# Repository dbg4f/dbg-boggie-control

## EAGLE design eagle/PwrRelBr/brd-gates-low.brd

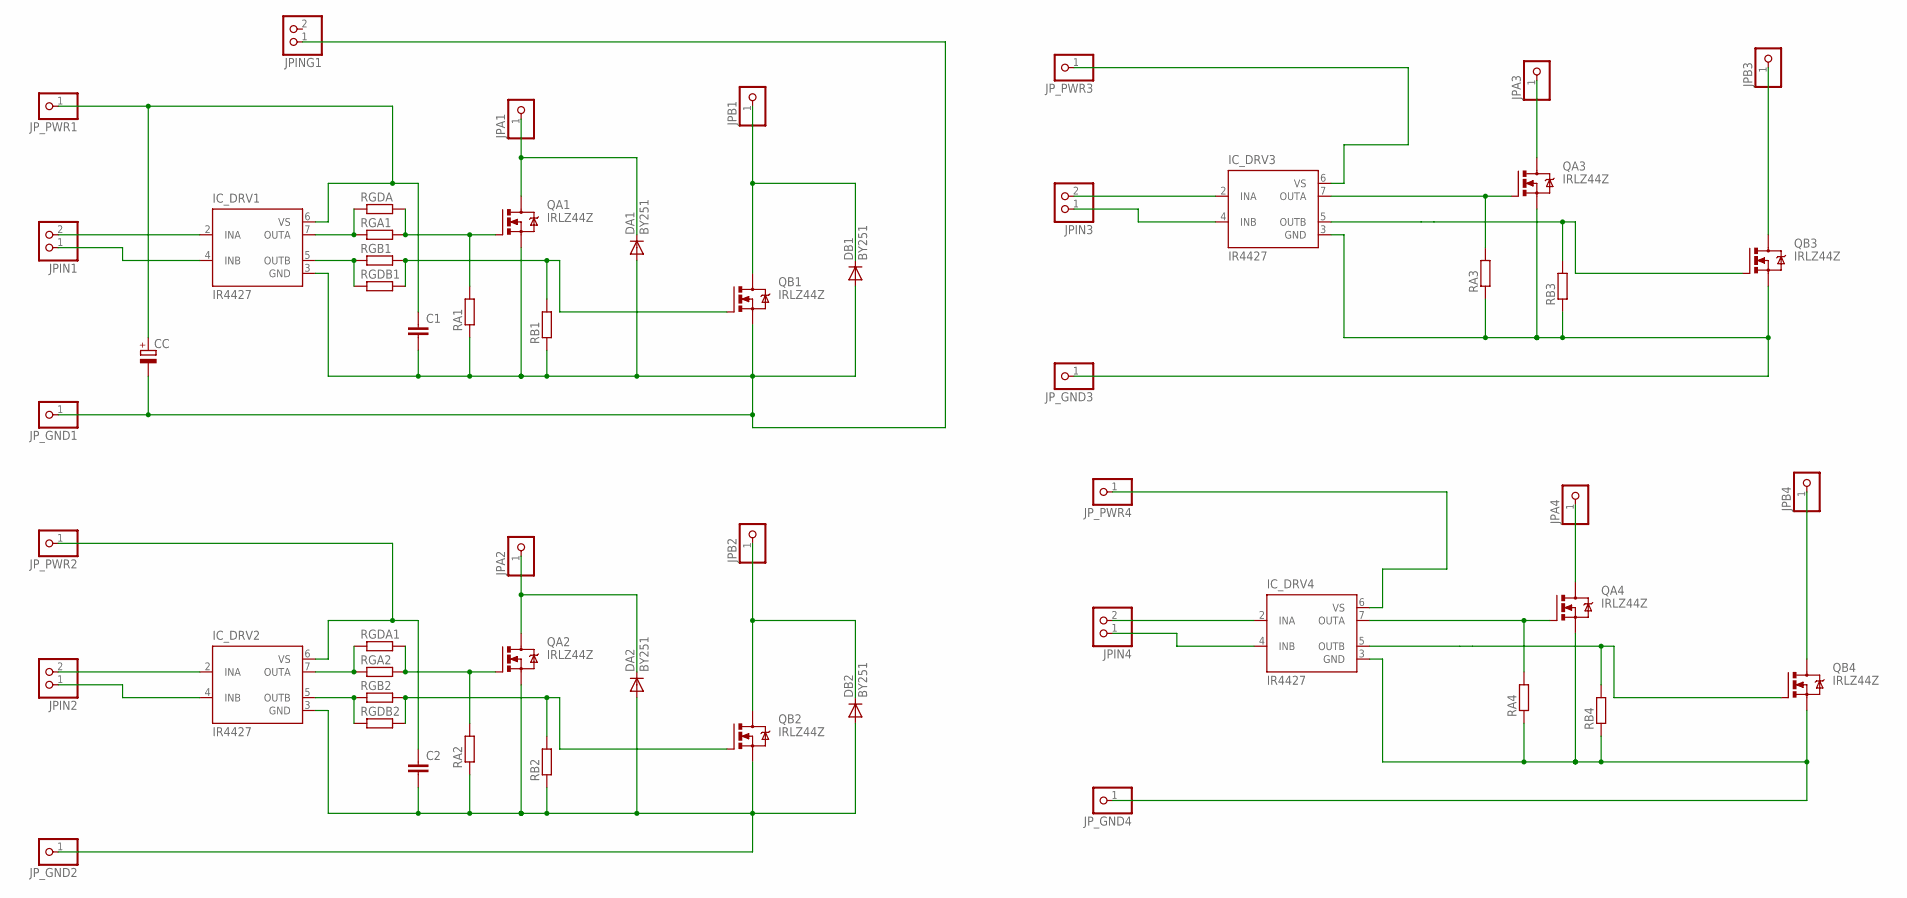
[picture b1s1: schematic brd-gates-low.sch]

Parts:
C1, C2: C-EU050-055X075; C050-055X075
CC: CPOL-EUE5-13; E5-13
DA1, DA2: BY251; DO201-15
DB1, DB2: BY251; DO201-15
IC_DRV1, IC_DRV2, IC_DRV3, IC_DRV4: IR4427; DIL08
JPA1, JPA2, JPA3, JPA4: PINHD-1X1; 1X01
JPB1, JPB2, JPB3, JPB4: PINHD-1X1; 1X01
JPIN1, JPIN2, JPIN3, JPIN4: PINHD-1X2; 1X02
JPING1: PINHD-1X2; 1X02
JP_GND1, JP_GND2, JP_GND3, JP_GND4: PINHD-1X1; 1X01
JP_PWR1, JP_PWR2, JP_PWR3, JP_PWR4: PINHD-1X1; 1X01
QA1, QA2, QA3, QA4: IRLZ44Z; TO220BH
QB1, QB2, QB3, QB4: IRLZ44Z; TO220BH
RA1, RA2, RA3, RA4: R-EU_0207/10; 0207/10
RB1, RB2, RB3, RB4: R-EU_0207/10; 0207/10
RGA1, RGA2: R-EU_0207/10; 0207/10
RGB1, RGB2: R-EU_0207/10; 0207/10
RGDA, RGDA1: R-EU_0207/10; 0207/10
RGDB1, RGDB2: R-EU_0207/10; 0207/10

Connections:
GND: C1.2, CC.-, DA1.A, DB1.A, IC_DRV1.3 (GND), JPING1.1, JP_GND1.1, QA1.S, QB1.S, RA1.1, RB1.1
GND1: C2.2, DA2.A, DB2.A, IC_DRV2.3 (GND), JP_GND2.1, QA2.S, QB2.S, RA2.1, RB2.1
GND2: IC_DRV3.3 (GND), JP_GND3.1, QA3.S, QB3.S, RA3.1, RB3.1
GND3: IC_DRV4.3 (GND), JP_GND4.1, QA4.S, QB4.S, RA4.1, RB4.1
unnamed: IC_DRV1.2 (INA), JPIN1.2
unnamed: IC_DRV1.4 (INB), JPIN1.1
unnamed: IC_DRV1.7 (OUTA), RGA1.1, RGDA.1
unnamed: IC_DRV1.5 (OUTB), RGB1.1, RGDB1.1
unnamed: QA1.G, RA1.2, RGA1.2, RGDA.2
unnamed: QB1.G, RB1.2, RGB1.2, RGDB1.2
unnamed: IC_DRV2.7 (OUTA), RGA2.1, RGDA1.1
unnamed: IC_DRV2.5 (OUTB), RGB2.1, RGDB2.1
unnamed: QA2.G, RA2.2, RGA2.2, RGDA1.2
unnamed: QB2.G, RB2.2, RGB2.2, RGDB2.2
unnamed: DA2.C, JPA2.1, QA2.D
unnamed: DB2.C, JPB2.1, QB2.D
unnamed: IC_DRV2.4 (INB), JPIN2.1
unnamed: IC_DRV2.2 (INA), JPIN2.2
unnamed: IC_DRV3.7 (OUTA), QA3.G, RA3.2
unnamed: IC_DRV3.5 (OUTB), QB3.G, RB3.2
unnamed: IC_DRV4.7 (OUTA), QA4.G, RA4.2
unnamed: IC_DRV4.5 (OUTB), QB4.G, RB4.2
unnamed: JPA3.1, QA3.D
unnamed: DB1.C, JPB1.1, QB1.D
unnamed: DA1.C, JPA1.1, QA1.D
unnamed: JPB3.1, QB3.D
unnamed: IC_DRV3.4 (INB), JPIN3.1
unnamed: IC_DRV3.2 (INA), JPIN3.2
unnamed: JPA4.1, QA4.D
unnamed: JPB4.1, QB4.D
unnamed: IC_DRV4.4 (INB), JPIN4.1
unnamed: IC_DRV4.2 (INA), JPIN4.2
VCC: C1.1, CC.+, IC_DRV1.6 (VS), JP_PWR1.1
VCC1: C2.1, IC_DRV2.6 (VS), JP_PWR2.1
VCC2: IC_DRV3.6 (VS), JP_PWR3.1
VCC3: IC_DRV4.6 (VS), JP_PWR4.1

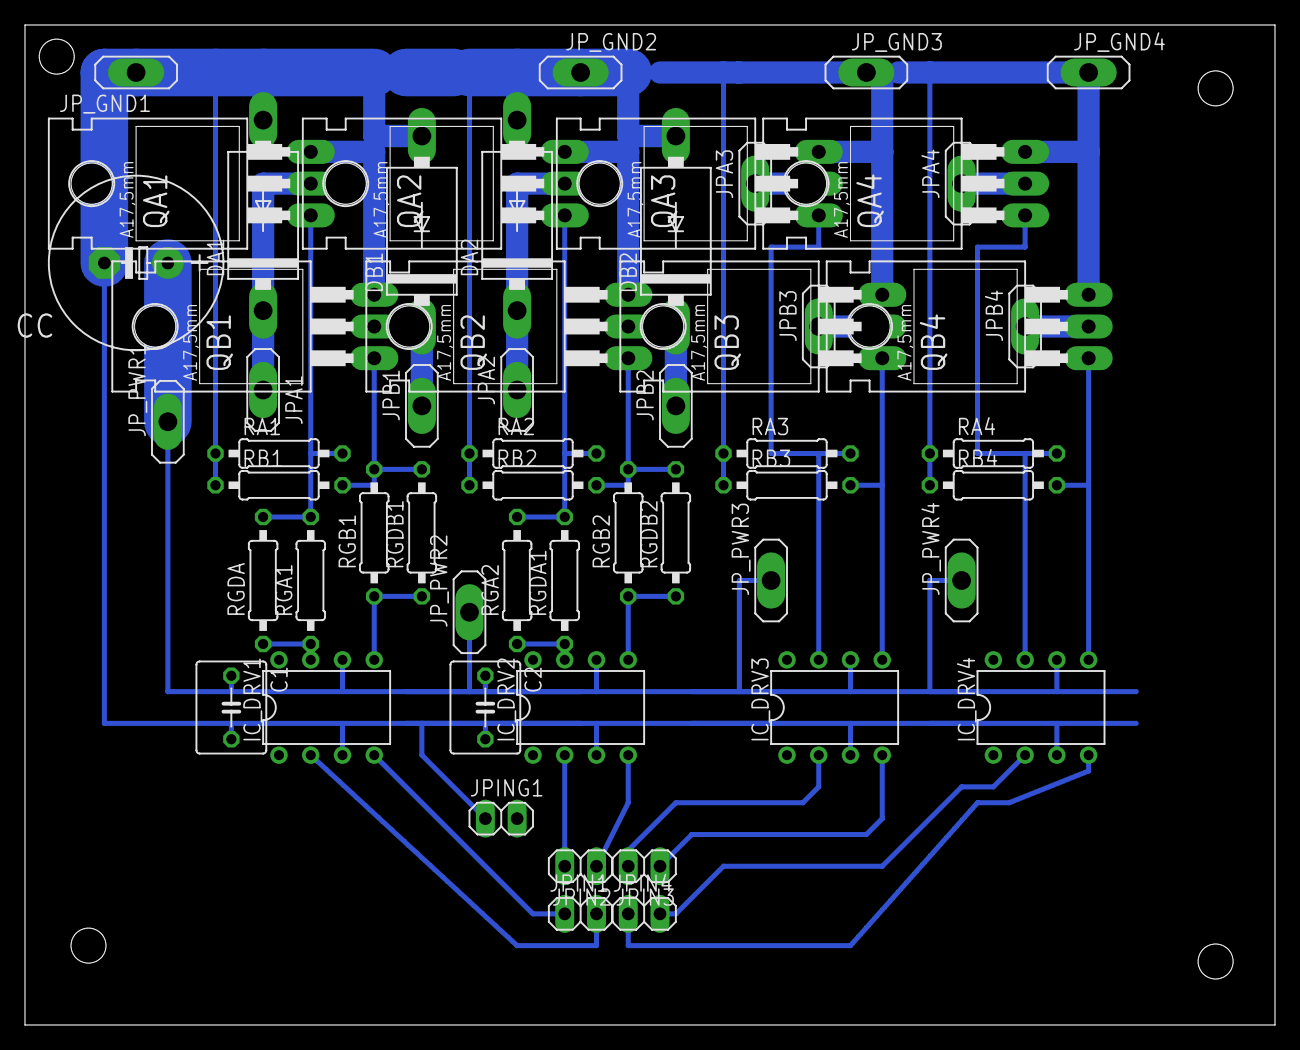
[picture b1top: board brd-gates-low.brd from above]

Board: 2 copper layers, 100.0 x 80.0 mm, 56 parts (0 on the bottom side), 36 nets.

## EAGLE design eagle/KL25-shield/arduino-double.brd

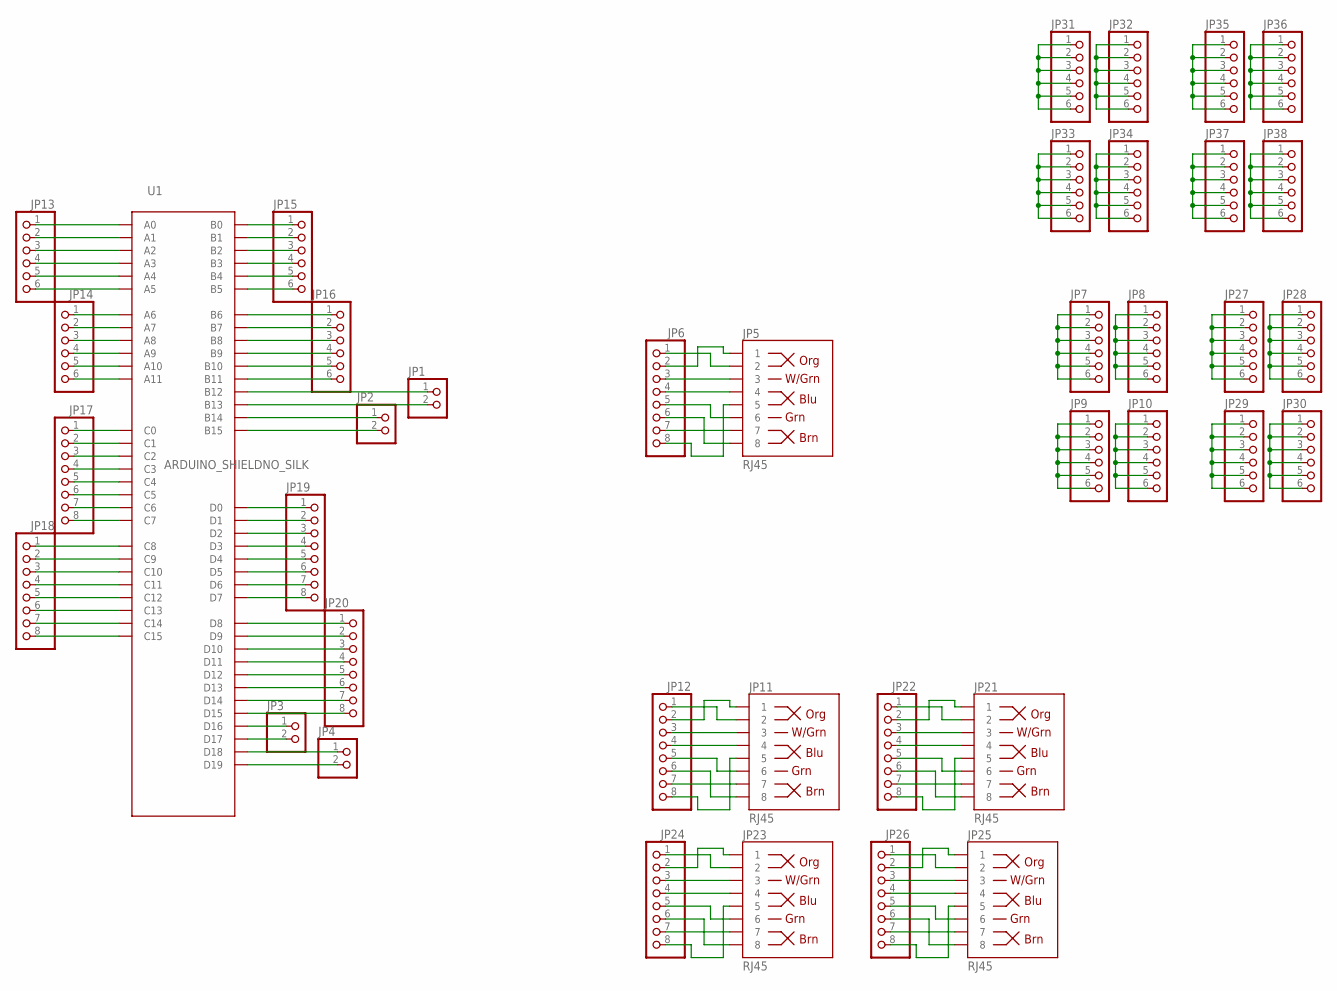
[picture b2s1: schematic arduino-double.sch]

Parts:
JP1, JP2, JP3, JP4: PINHD-1X2; 1X02
JP5, JP11, JP21, JP23, JP25: RJ45; RJ45-8
JP6, JP12, JP17, JP18, JP19, JP20, JP22, JP24, JP26: PINHD-1X8; 1X08
JP7, JP8, JP9, JP10, JP13, JP14, JP15, JP16, JP27, JP28, JP29, JP30, JP31, JP32, JP33, JP34, JP35, JP36, JP37, JP38: PINHD-1X6; 1X06
U1: ARDUINO_SHIELDNO_SILK; DUEMILANOVE_VIAS

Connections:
unnamed: JP13.1, U1.A0
unnamed: JP13.2, U1.A1
unnamed: JP13.3, U1.A2
unnamed: JP13.4, U1.A3
unnamed: JP13.5, U1.A4
unnamed: JP13.6, U1.A5
unnamed: JP14.1, U1.A6
unnamed: JP14.2, U1.A7
unnamed: JP14.3, U1.A8
unnamed: JP14.4, U1.A9
unnamed: JP14.5, U1.A10
unnamed: JP14.6, U1.A11
unnamed: JP15.1, U1.B0
unnamed: JP15.2, U1.B1
unnamed: JP15.3, U1.B2
unnamed: JP15.4, U1.B3
unnamed: JP15.5, U1.B4
unnamed: JP15.6, U1.B5
unnamed: JP16.1, U1.B6
unnamed: JP16.2, U1.B7
unnamed: JP16.3, U1.B8
unnamed: JP16.4, U1.B9
unnamed: JP16.5, U1.B10
unnamed: JP16.6, U1.B11
unnamed: JP19.1, U1.D0
unnamed: JP19.2, U1.D1
unnamed: JP19.3, U1.D2
unnamed: JP19.4, U1.D3
unnamed: JP19.5, U1.D4
unnamed: JP19.6, U1.D5
unnamed: JP19.7, U1.D6
unnamed: JP19.8, U1.D7
unnamed: JP20.1, U1.D8
unnamed: JP20.2, U1.D9
unnamed: JP20.3, U1.D10
unnamed: JP20.4, U1.D11
unnamed: JP20.5, U1.D12
unnamed: JP20.6, U1.D13
unnamed: JP20.7, U1.D14
unnamed: JP20.8, U1.D15
unnamed: JP18.1, U1.C8
unnamed: JP18.2, U1.C9
unnamed: JP18.3, U1.C10
unnamed: JP18.4, U1.C11
unnamed: JP18.5, U1.C12
unnamed: JP18.6, U1.C13
unnamed: JP18.7, U1.C14
unnamed: JP18.8, U1.C15
unnamed: JP17.8, U1.C7
unnamed: JP17.7, U1.C6
unnamed: JP17.6, U1.C5
unnamed: JP17.5, U1.C4
unnamed: JP17.4, U1.C3
unnamed: JP17.3, U1.C2
unnamed: JP17.2, U1.C1
unnamed: JP17.1, U1.C0
unnamed: JP1.1, U1.B12
unnamed: JP1.2, U1.B13
unnamed: JP2.1, U1.B14
unnamed: JP2.2, U1.B15
unnamed: JP3.1, U1.D16
unnamed: JP3.2, U1.D17
unnamed: JP4.1, U1.D18
unnamed: JP4.2, U1.D19
unnamed: JP7.1, JP7.2, JP7.3, JP7.4, JP7.5, JP7.6
unnamed: JP8.1, JP8.2, JP8.3, JP8.4, JP8.5, JP8.6
unnamed: JP9.1, JP9.2, JP9.3, JP9.4, JP9.5, JP9.6
unnamed: JP10.1, JP10.2, JP10.3, JP10.4, JP10.5, JP10.6
unnamed: JP5.3, JP6.3
unnamed: JP5.4, JP6.4
unnamed: JP5.6, JP6.5
unnamed: JP5.8, JP6.6
unnamed: JP5.1, JP6.2
unnamed: JP5.5, JP6.8
unnamed: JP5.7, JP6.7
unnamed: JP5.2, JP6.1
unnamed: JP27.1, JP27.2, JP27.3, JP27.4, JP27.5, JP27.6
unnamed: JP28.1, JP28.2, JP28.3, JP28.4, JP28.5, JP28.6
unnamed: JP29.1, JP29.2, JP29.3, JP29.4, JP29.5, JP29.6
unnamed: JP30.1, JP30.2, JP30.3, JP30.4, JP30.5, JP30.6
unnamed: JP31.1, JP31.2, JP31.3, JP31.4, JP31.5, JP31.6
unnamed: JP32.1, JP32.2, JP32.3, JP32.4, JP32.5, JP32.6
unnamed: JP33.1, JP33.2, JP33.3, JP33.4, JP33.5, JP33.6
unnamed: JP34.1, JP34.2, JP34.3, JP34.4, JP34.5, JP34.6
unnamed: JP35.1, JP35.2, JP35.3, JP35.4, JP35.5, JP35.6
unnamed: JP36.1, JP36.2, JP36.3, JP36.4, JP36.5, JP36.6
unnamed: JP37.1, JP37.2, JP37.3, JP37.4, JP37.5, JP37.6
unnamed: JP38.1, JP38.2, JP38.3, JP38.4, JP38.5, JP38.6
unnamed: JP11.3, JP12.3
unnamed: JP11.4, JP12.4
unnamed: JP11.6, JP12.5
unnamed: JP11.8, JP12.6
unnamed: JP11.1, JP12.2
unnamed: JP11.5, JP12.8
unnamed: JP11.7, JP12.7
unnamed: JP11.2, JP12.1
unnamed: JP21.3, JP22.3
unnamed: JP21.4, JP22.4
unnamed: JP21.6, JP22.5
unnamed: JP21.8, JP22.6
unnamed: JP21.1, JP22.2
unnamed: JP21.5, JP22.8
unnamed: JP21.7, JP22.7
unnamed: JP21.2, JP22.1
unnamed: JP23.3, JP24.3
unnamed: JP23.4, JP24.4
unnamed: JP23.6, JP24.5
unnamed: JP23.8, JP24.6
unnamed: JP23.1, JP24.2
unnamed: JP23.5, JP24.8
unnamed: JP23.7, JP24.7
unnamed: JP23.2, JP24.1
unnamed: JP25.3, JP26.3
unnamed: JP25.4, JP26.4
unnamed: JP25.6, JP26.5
unnamed: JP25.8, JP26.6
unnamed: JP25.1, JP26.2
unnamed: JP25.5, JP26.8
unnamed: JP25.7, JP26.7
unnamed: JP25.2, JP26.1

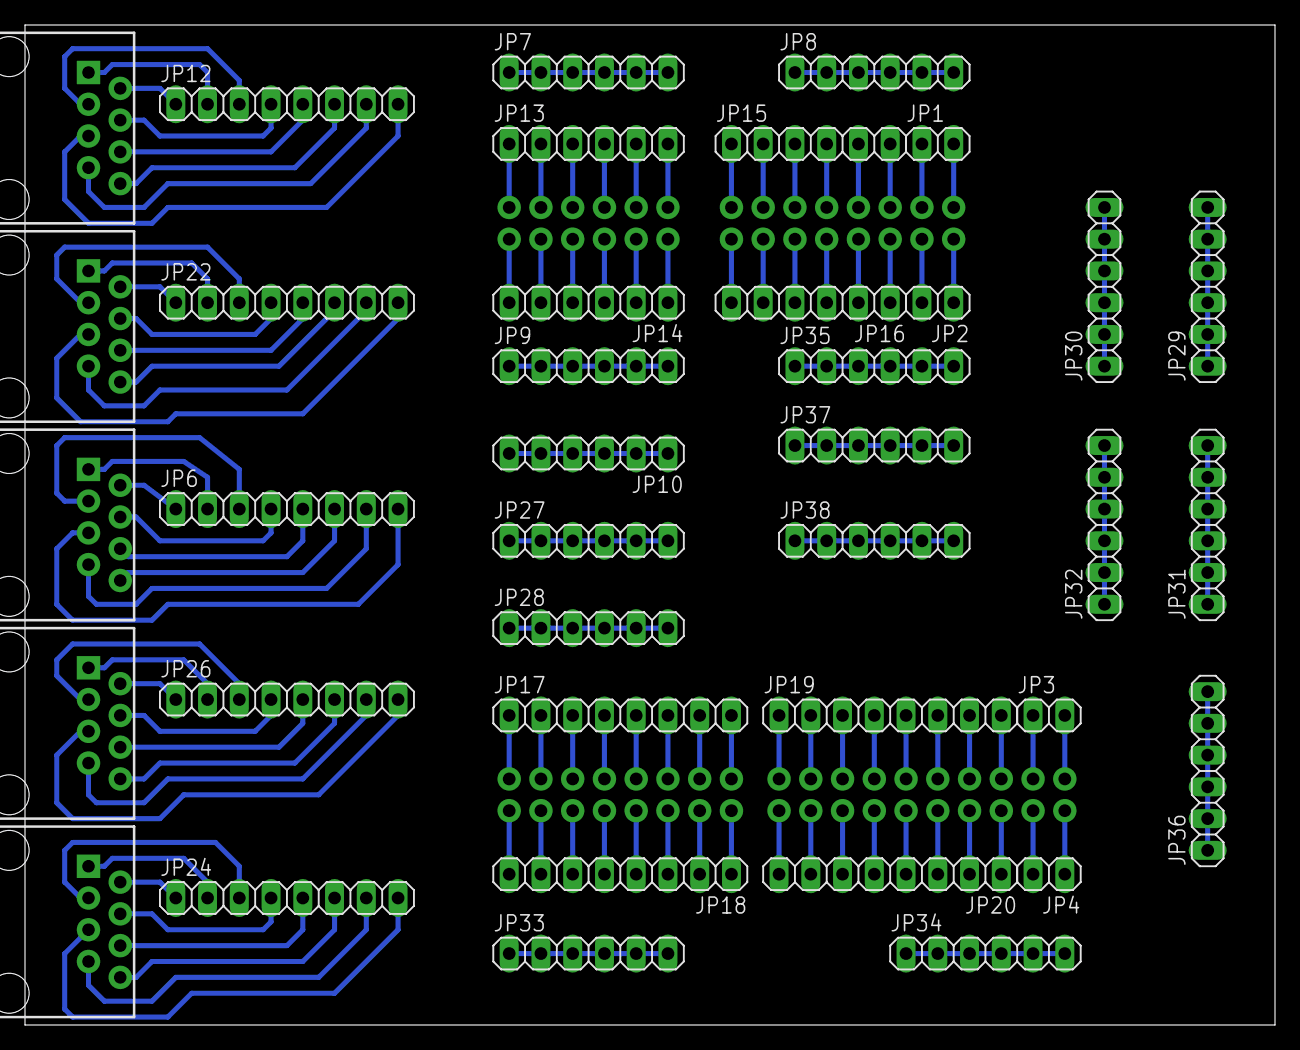
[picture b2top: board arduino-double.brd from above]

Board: 2 copper layers, 100.0 x 80.0 mm, 39 parts (0 on the bottom side), 120 nets.

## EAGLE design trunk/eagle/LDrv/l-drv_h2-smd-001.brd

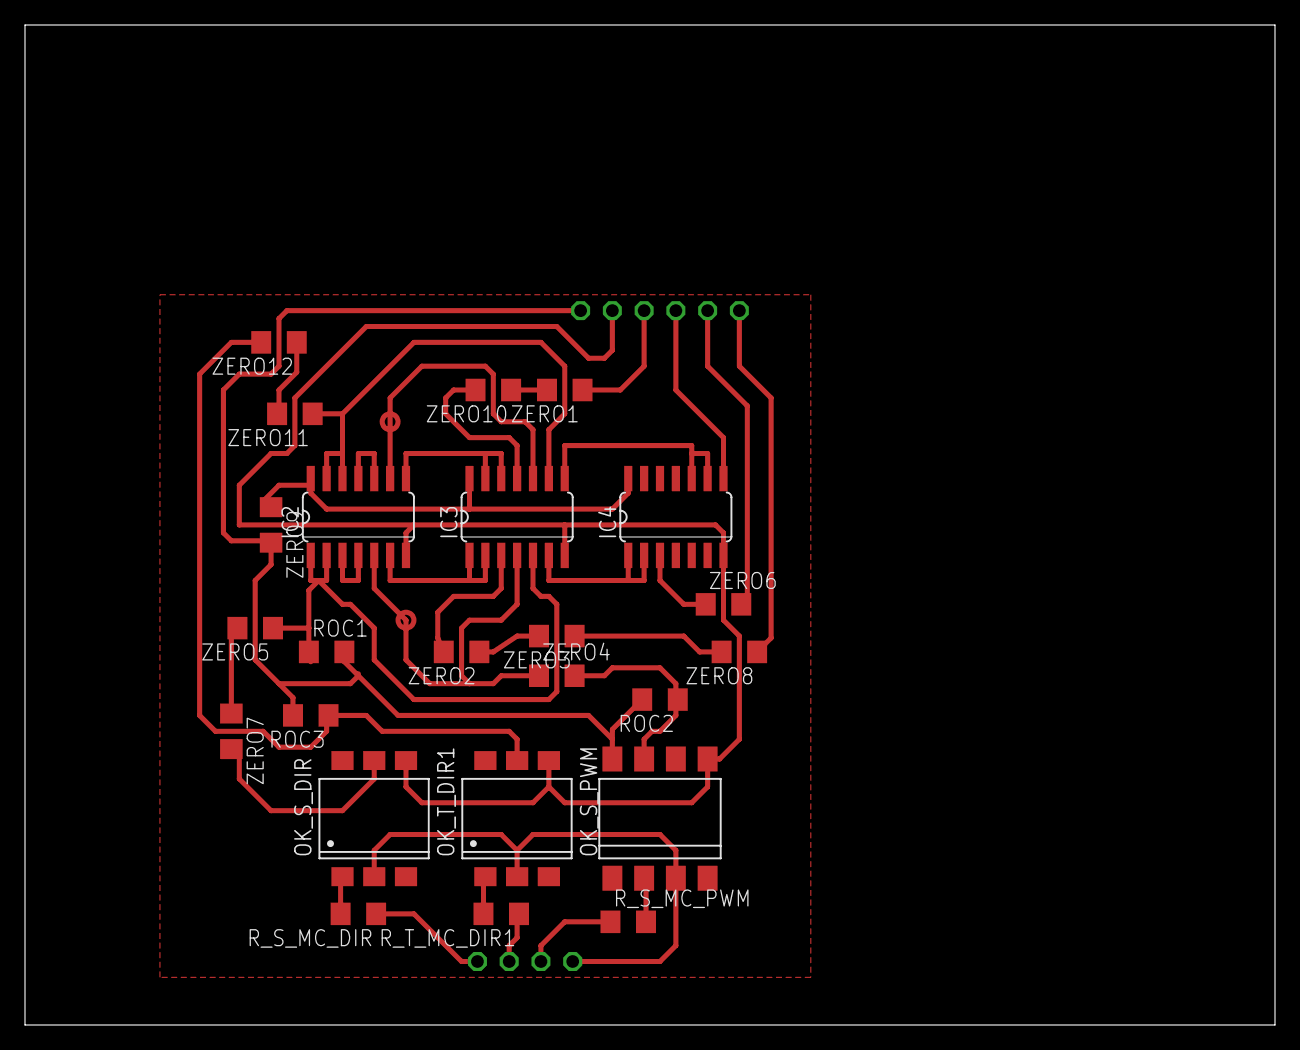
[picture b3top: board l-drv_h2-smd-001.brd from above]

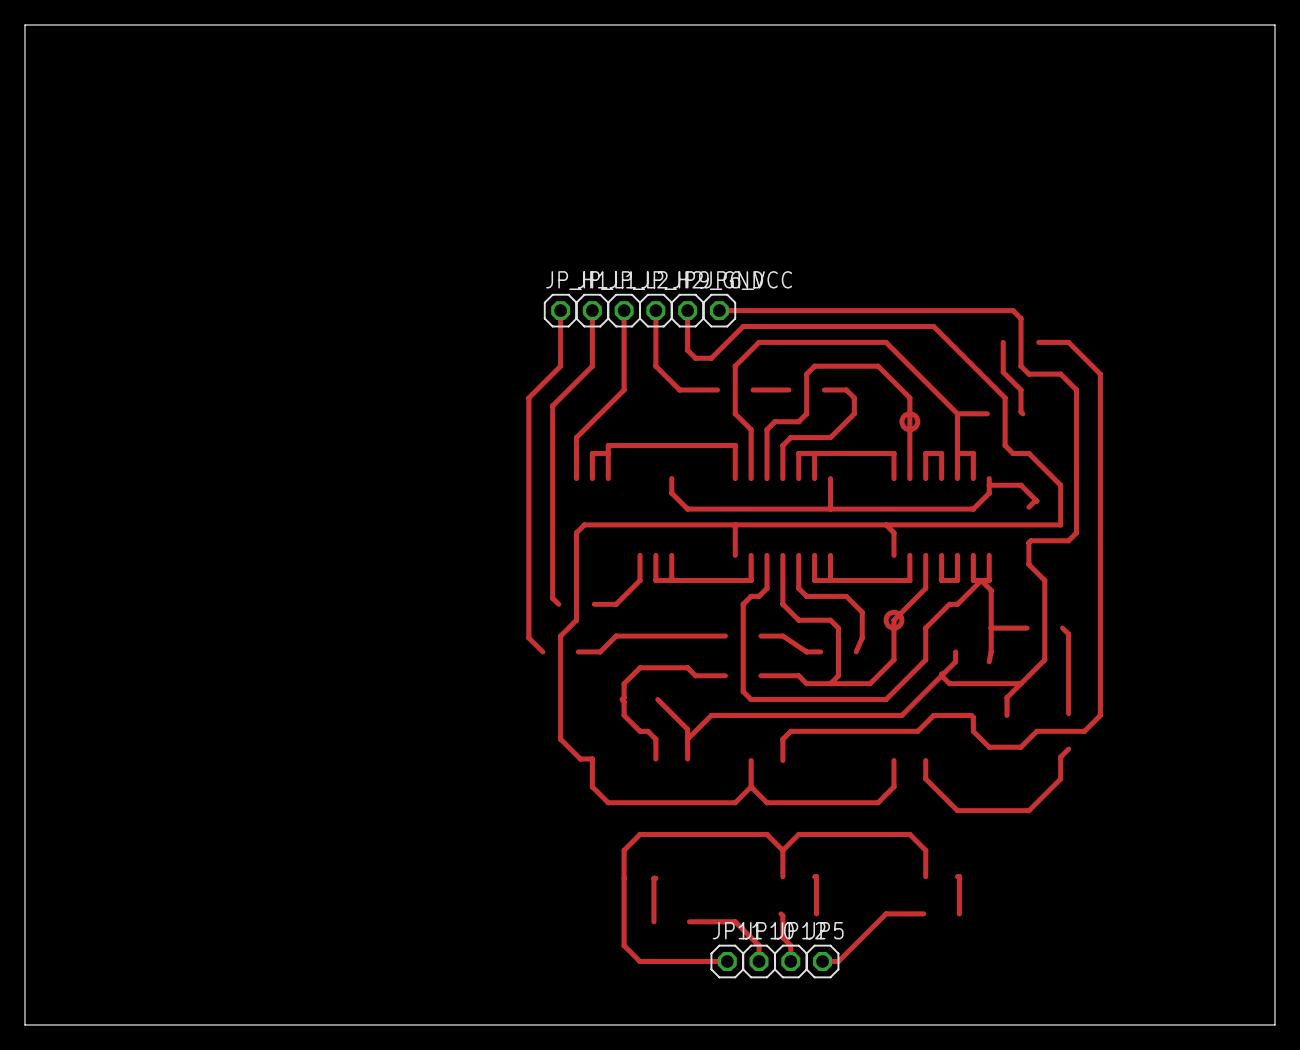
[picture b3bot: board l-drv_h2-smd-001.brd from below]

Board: 2 copper layers, 100.0 x 80.0 mm, 34 parts (10 on the bottom side), 34 nets.

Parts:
IC2, IC3, IC4: 74AC132D; SO14
JP5, JP6_VCC, JP9_GND, JP10, JP11, JP12: 1X01
JP_H1, JP_H2: 1X01
JP_L1, JP_L2: 1X01
OK_S_DIR: 4N25SM; DIL6-SMD
OK_S_PWM: 6N137DIL8-SMD-6N137; DIL8-SMD
OK_T_DIR1: 4N25SM; DIL6-SMD
ROC1, ROC2, ROC3: R1206
R_S_MC_DIR: R1206
R_S_MC_PWM: R1206
R_T_MC_DIR1: R1206
ZERO1, ZERO2, ZERO3, ZERO4, ZERO5, ZERO6, ZERO7, ZERO8, ZERO9, ZERO10, ZERO11, ZERO12: R1206

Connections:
GND: IC2.7, IC3.7, IC4.7, JP9_GND.1, OK_S_DIR.4, OK_S_PWM.5, OK_T_DIR1.4
MC_GND: JP11.1, OK_S_DIR.2, OK_S_PWM.3, OK_T_DIR1.2
unnamed: OK_S_DIR.1, R_S_MC_DIR.2
unnamed: OK_S_PWM.2, R_S_MC_PWM.2
unnamed: OK_T_DIR1.1, R_T_MC_DIR1.2
unnamed: IC3.3, ZERO2.2
unnamed: IC2.3, IC2.4
unnamed: JP5.1, R_S_MC_DIR.1
unnamed: JP10.1, R_S_MC_PWM.1
unnamed: JP12.1, R_T_MC_DIR1.1
unnamed: IC2.10, IC2.11
unnamed: ZERO1.2, ZERO10.1
unnamed: IC2.6, IC3.1, IC3.2
unnamed: IC2.8, IC3.12, IC3.13
unnamed: JP_H2.1, ZERO1.1
unnamed: JP_H1.1, ZERO8.1
unnamed: IC3.11, ZERO10.2
unnamed: ZERO2.1, ZERO3.2
unnamed: IC4.3, ZERO6.1
unnamed: IC4.8, JP_L2.1
unnamed: IC3.6, IC4.1, IC4.2
unnamed: OK_S_PWM.7, ROC2.1, ZERO4.2
unnamed: IC3.8, IC4.9, IC4.10
unnamed: ZERO5.2, ZERO7.1
unnamed: JP_L1.1, ZERO6.2
unnamed: OK_S_DIR.5, ZERO7.2
unnamed: ZERO3.1, ZERO8.2
unnamed: JP6_VCC.1, OK_S_PWM.8, ROC1.2, ROC2.2, ROC3.2, ZERO9.2
unnamed: OK_T_DIR1.5, ROC3.1, ZERO12.2
unnamed: ZERO11.2, ZERO12.1
N$D1: IC2.1, IC2.2, IC3.5, ROC1.1, ZERO5.1
N$D2: IC2.12, IC2.13, IC3.9, ZERO11.1
N$PWM: IC2.5, IC2.9, IC3.4, IC3.10, ZERO4.1
VCC: IC2.14, IC3.14, IC4.14, ZERO9.1

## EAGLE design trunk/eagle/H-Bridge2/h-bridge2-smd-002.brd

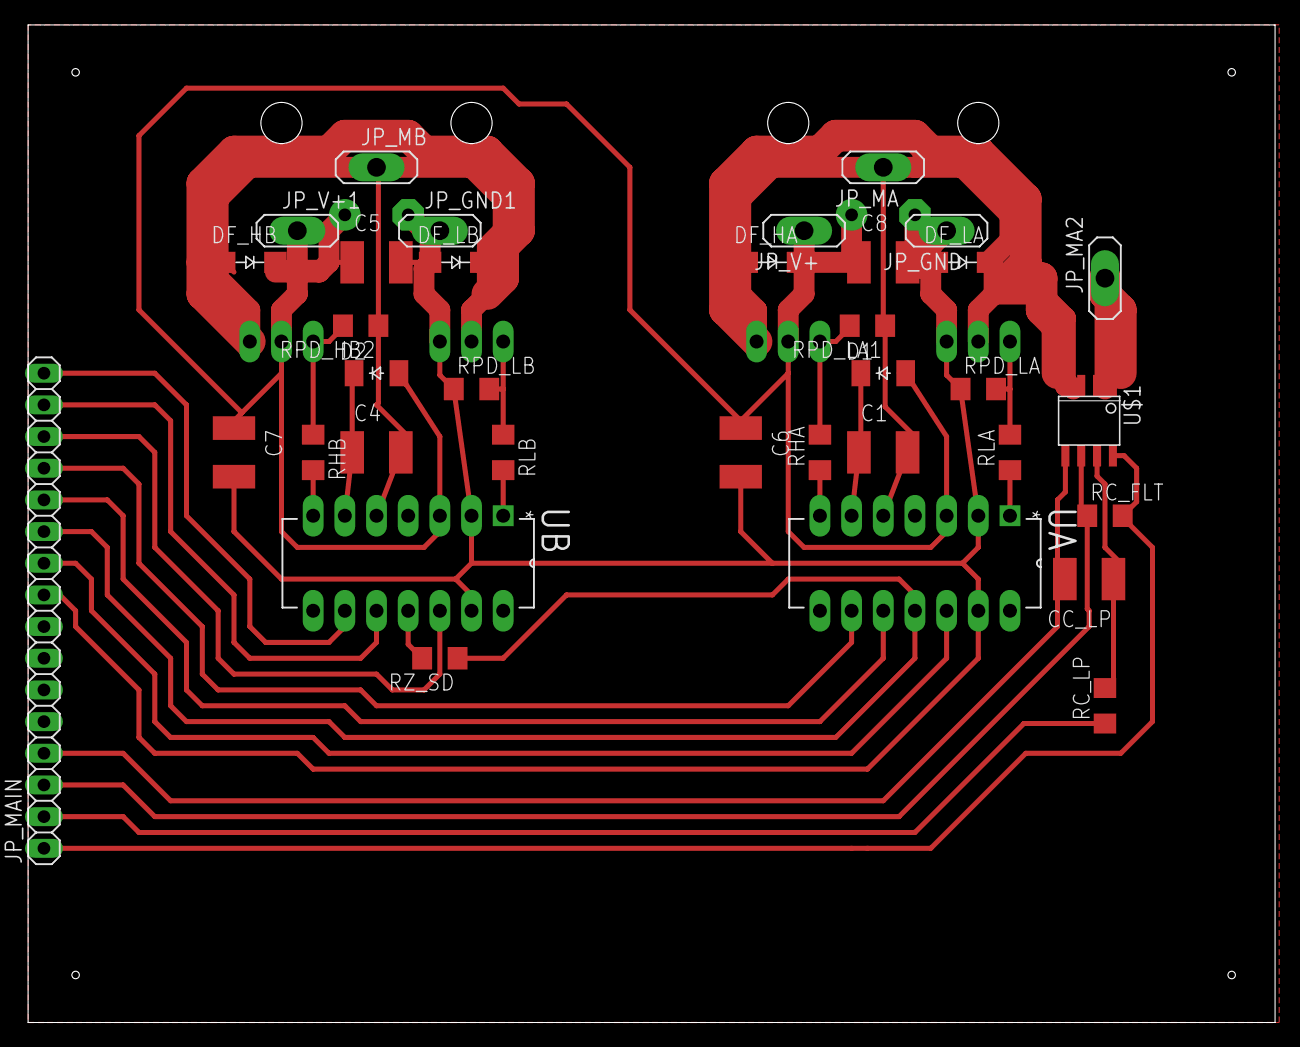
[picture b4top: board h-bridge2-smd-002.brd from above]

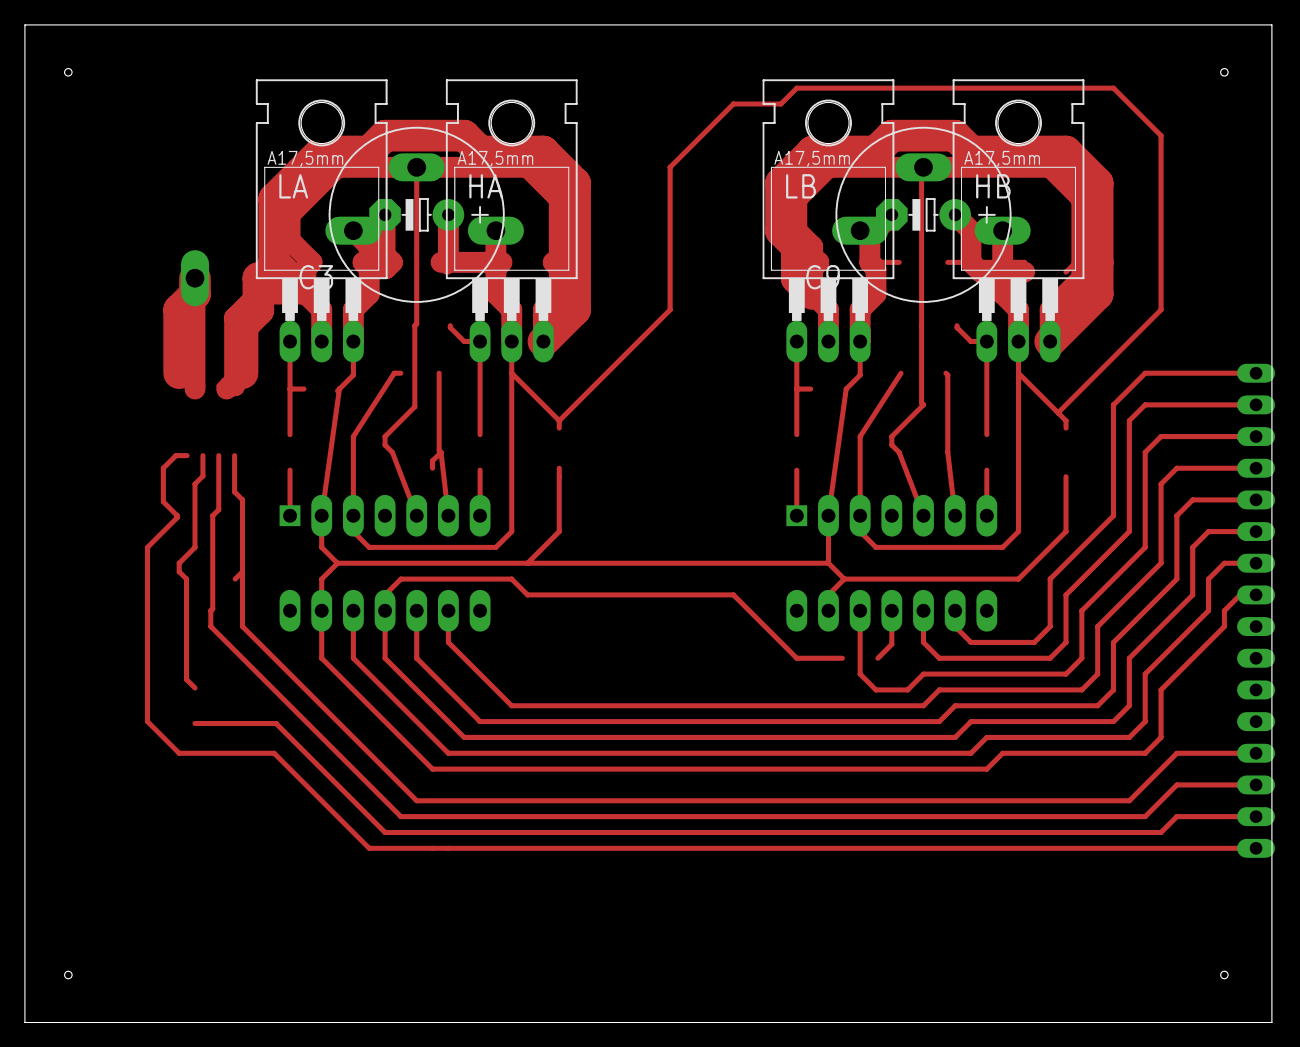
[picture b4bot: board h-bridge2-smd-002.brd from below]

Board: 2 copper layers, 100.0 x 80.0 mm, 41 parts (6 on the bottom side), 28 nets.

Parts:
C1, C4, C5, C6, C7, C8: C4532
C3, C9: E5-13
CC_LP: C4532
D1, D2: CGRM4001-G; SOD-123_MINI-SMA
DF_HA: GF1; SMA-DO214AC
DF_HB: GF1; SMA-DO214AC
DF_LA: GF1; SMA-DO214AC
DF_LB: GF1; SMA-DO214AC
HA: IRLZ44Z; TO220BH
HB: IRLZ44Z; TO220BH
JP_GND, JP_GND1: 1X01
JP_MA, JP_MA2: 1X01
JP_MAIN: 1X16
JP_MB: 1X01
JP_V+, JP_V+1: 1X01
LA: IRLZ44Z; TO220BH
LB: IRLZ44Z; TO220BH
RC_FLT: R1206
RC_LP: R1206
RHA: R1206
RHB: R1206
RLA: R1206
RLB: R1206
RPD_HB2: R1206
RPD_LA, RPD_LA1: R1206
RPD_LB: R1206
RZ_SD: R1206
U$1: ACS711; SOIC8
UA: IR2110PBF; DIP254P762X533-14
UB: IR2110PBF; DIP254P762X533-14

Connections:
unnamed: JP_MA2.1, U$1.1, U$1.2
unnamed: JP_MAIN.1, RC_FLT.2, U$1.8
unnamed: JP_MAIN.3, RC_FLT.1, U$1.6
unnamed: C3.-, C5.2, C6.2, C7.2, C8.2, C9.-, DF_LA.A, DF_LB.A, JP_GND.1, JP_GND1.1, JP_MAIN.9, LA.S, LB.S, RPD_LA.1, RPD_LB.1, UA.2, UA.13, UB.2, UB.13
unnamed: LA.G, RLA.2, RPD_LA.2
unnamed: HA.G, RHA.2, RPD_LA1.2
unnamed: HB.G, RHB.1, RPD_HB2.2
unnamed: LB.G, RLB.1, RPD_LB.2
unnamed: RHA.1, UA.7
unnamed: RLA.1, UA.1
unnamed: RHB.2, UB.7
unnamed: RLB.2, UB.1
unnamed: C3.+, C5.1, C6.1, C7.1, C8.1, C9.+, D1.A, D2.A, DF_HA.K, DF_HB.K, HA.D, HB.D, JP_V+.1, JP_V+1.1, UA.3, UB.3
unnamed: C1.1, D1.C, UA.6
unnamed: CC_LP.1, RC_LP.2, U$1.7
unnamed: C1.2, DF_HA.A, DF_LA.K, HA.S, JP_MA.1, LA.D, RPD_LA1.1, U$1.3, U$1.4, UA.5
unnamed: C4.1, D2.C, UB.6
unnamed: JP_MAIN.2, RC_LP.1
unnamed: JP_MAIN.11, RZ_SD.1, UA.11
unnamed: CC_LP.2, JP_MAIN.4, U$1.5
unnamed: JP_MAIN.13, UA.9
unnamed: JP_MAIN.12, UA.10
unnamed: JP_MAIN.10, UA.12
unnamed: JP_MAIN.16, UB.9
unnamed: JP_MAIN.15, UB.10
unnamed: JP_MAIN.14, UB.12
unnamed: RZ_SD.2, UB.11
unnamed: C4.2, DF_HB.A, DF_LB.K, HB.S, JP_MB.1, LB.D, RPD_HB2.1, UB.5

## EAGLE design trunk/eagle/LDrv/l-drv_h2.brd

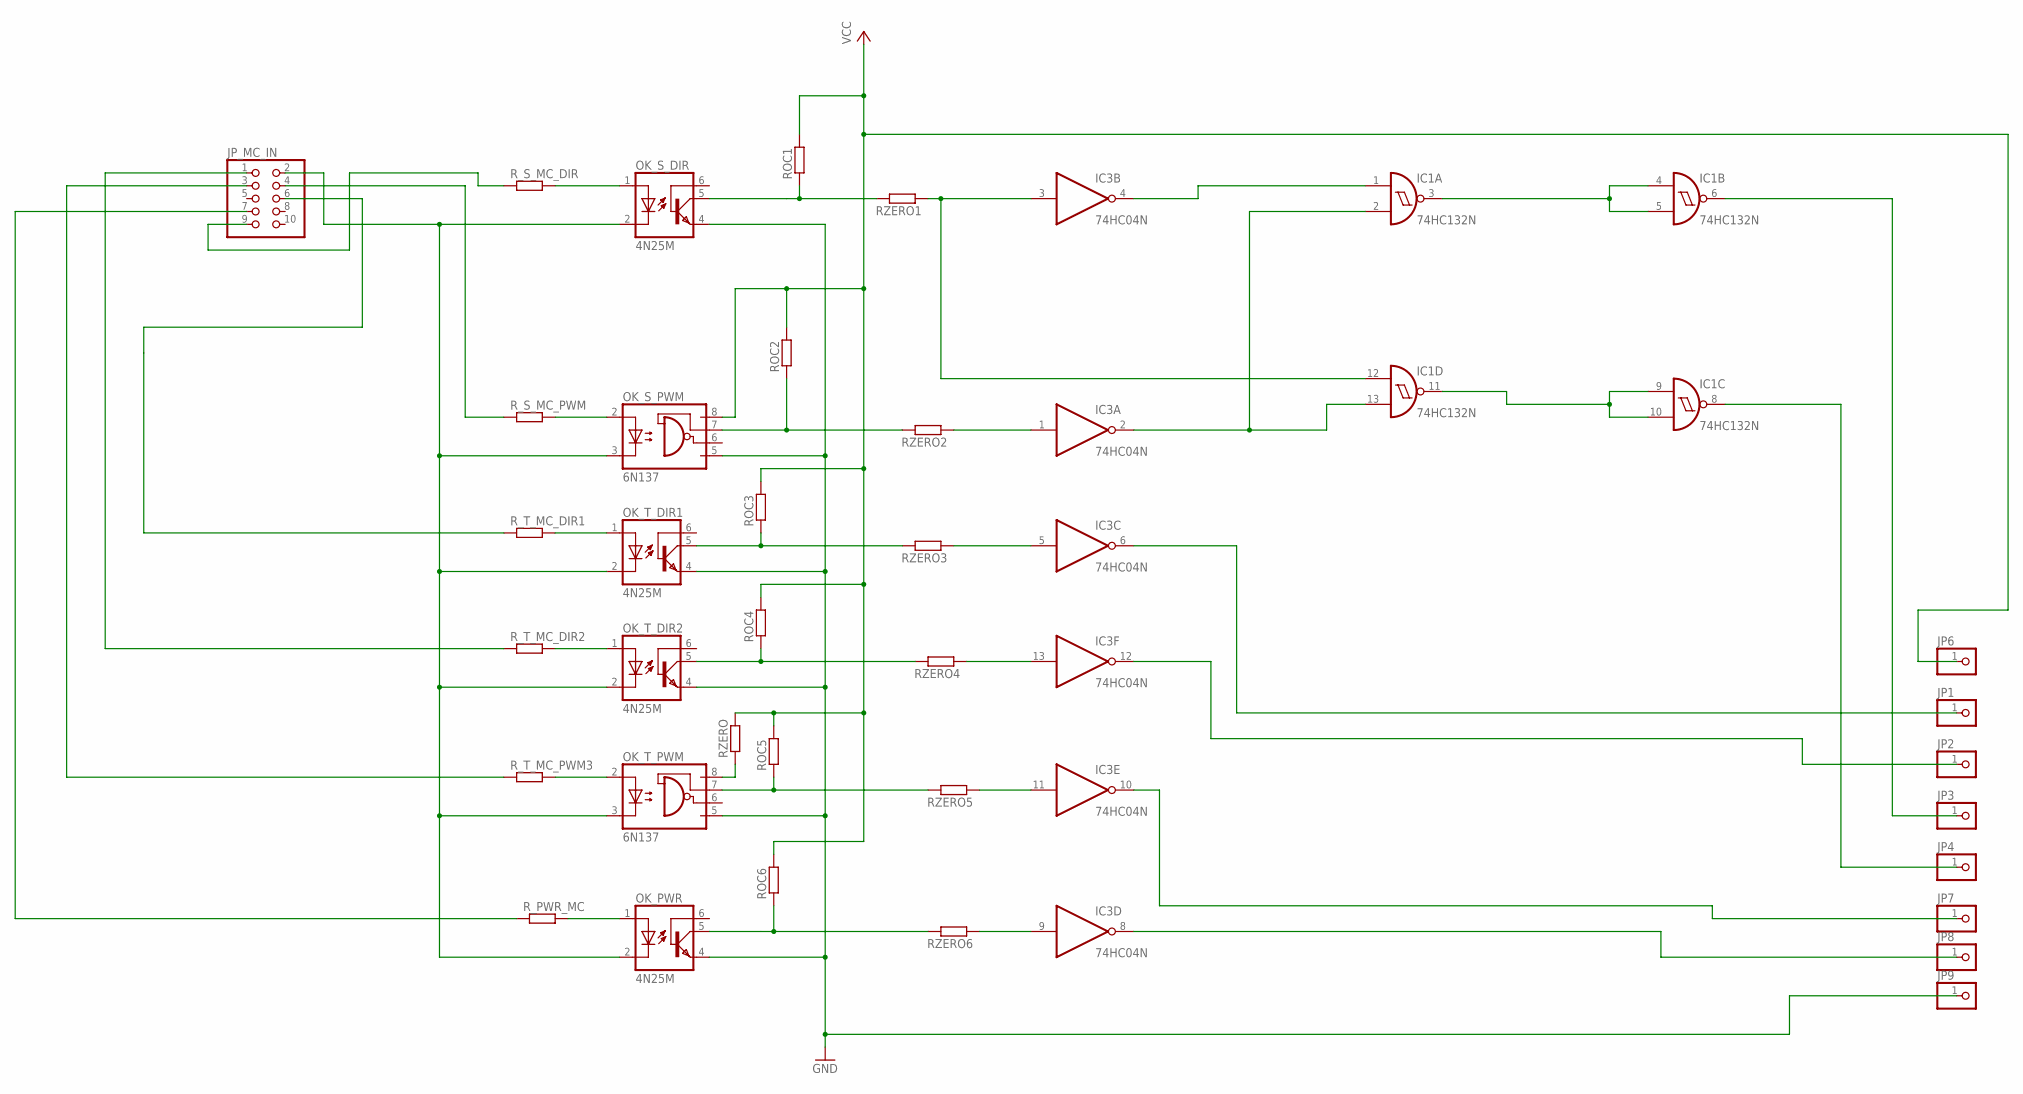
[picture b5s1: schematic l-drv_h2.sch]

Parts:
IC1: 74HC132N; DIL14
IC3: 74HC04N; DIL14
JP1, JP2, JP3, JP4, JP6, JP7, JP8, JP9: PINHD-1X1; 1X01
JP_MC_IN: PINHD-2X5; 2X05
OK_PWR: 4N25M; DIL06
OK_S_DIR: 4N25M; DIL06
OK_S_PWM: 6N137; DIL08
OK_T_DIR1, OK_T_DIR2: 4N25M; DIL06
OK_T_PWM: 6N137; DIL08
ROC1, ROC2, ROC3, ROC4, ROC5, ROC6: R-EU_0204/5; 0204/5
RZERO, RZERO1, RZERO2, RZERO3, RZERO4, RZERO5, RZERO6: R-EU_0204/5; 0204/5
R_PWR_MC: R-EU_0204/5; 0204/5
R_S_MC_DIR: R-EU_0204/5; 0204/5
R_S_MC_PWM: R-EU_0204/5; 0204/5
R_T_MC_DIR1, R_T_MC_DIR2: R-EU_0204/5; 0204/5
R_T_MC_PWM3: R-EU_0204/5; 0204/5

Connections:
GND: IC1.7 (GND), IC3.7 (GND), JP9.1, OK_PWR.4 (EMI), OK_S_DIR.4 (EMI), OK_S_PWM.5 (GND), OK_T_DIR1.4 (EMI), OK_T_DIR2.4 (EMI), OK_T_PWM.5 (GND)
MC_GND: JP_MC_IN.2, OK_PWR.2 (C), OK_S_DIR.2 (C), OK_S_PWM.3 (C), OK_T_DIR1.2 (C), OK_T_DIR2.2 (C), OK_T_PWM.3 (C)
unnamed: OK_S_DIR.1 (A), R_S_MC_DIR.2
unnamed: OK_S_PWM.2 (A), R_S_MC_PWM.2
unnamed: OK_T_DIR1.1 (A), R_T_MC_DIR1.2
unnamed: OK_T_DIR2.1 (A), R_T_MC_DIR2.2
unnamed: OK_T_PWM.2 (A), R_T_MC_PWM3.2
unnamed: JP_MC_IN.9, R_S_MC_DIR.1
unnamed: JP_MC_IN.4, R_S_MC_PWM.1
unnamed: JP_MC_IN.6, R_T_MC_DIR1.1
unnamed: JP_MC_IN.1, R_T_MC_DIR2.1
unnamed: JP_MC_IN.3, R_T_MC_PWM3.1
unnamed: OK_T_DIR1.5 (COL), ROC3.1, RZERO3.2
unnamed: IC1.12 (I0), IC3.3 (I), RZERO1.1
unnamed: OK_T_PWM.7 (VE), ROC5.1, RZERO5.2
unnamed: OK_PWR.1 (A), R_PWR_MC.2
unnamed: OK_T_DIR2.5 (COL), ROC4.1, RZERO4.2
unnamed: JP_MC_IN.7, R_PWR_MC.1
unnamed: OK_S_PWM.7 (VE), ROC2.1, RZERO2.2
unnamed: OK_S_DIR.5 (COL), ROC1.1, RZERO1.2
unnamed: OK_PWR.5 (COL), ROC6.1, RZERO6.2
unnamed: IC3.8 (O), JP8.1
unnamed: IC3.10 (O), JP7.1
unnamed: IC3.12 (O), JP2.1
unnamed: IC3.6 (O), JP1.1
unnamed: IC1.6 (O), JP3.1
unnamed: IC1.8 (O), JP4.1
unnamed: IC1.2 (I1), IC1.13 (I1), IC3.2 (O)
unnamed: IC1.1 (I0), IC3.4 (O)
unnamed: IC1.3 (O), IC1.4 (I0), IC1.5 (I1)
unnamed: IC1.9 (I0), IC1.10 (I1), IC1.11 (O)
unnamed: IC3.1 (I), RZERO2.1
unnamed: IC3.5 (I), RZERO3.1
unnamed: IC3.13 (I), RZERO4.1
unnamed: IC3.11 (I), RZERO5.1
unnamed: IC3.9 (I), RZERO6.1
unnamed: OK_T_PWM.8 (VCC), RZERO.1
VCC: IC1.14 (VCC), IC3.14 (VCC), JP6.1, OK_S_PWM.8 (VCC), ROC1.2, ROC2.2, ROC3.2, ROC4.2, ROC5.2, ROC6.2, RZERO.2

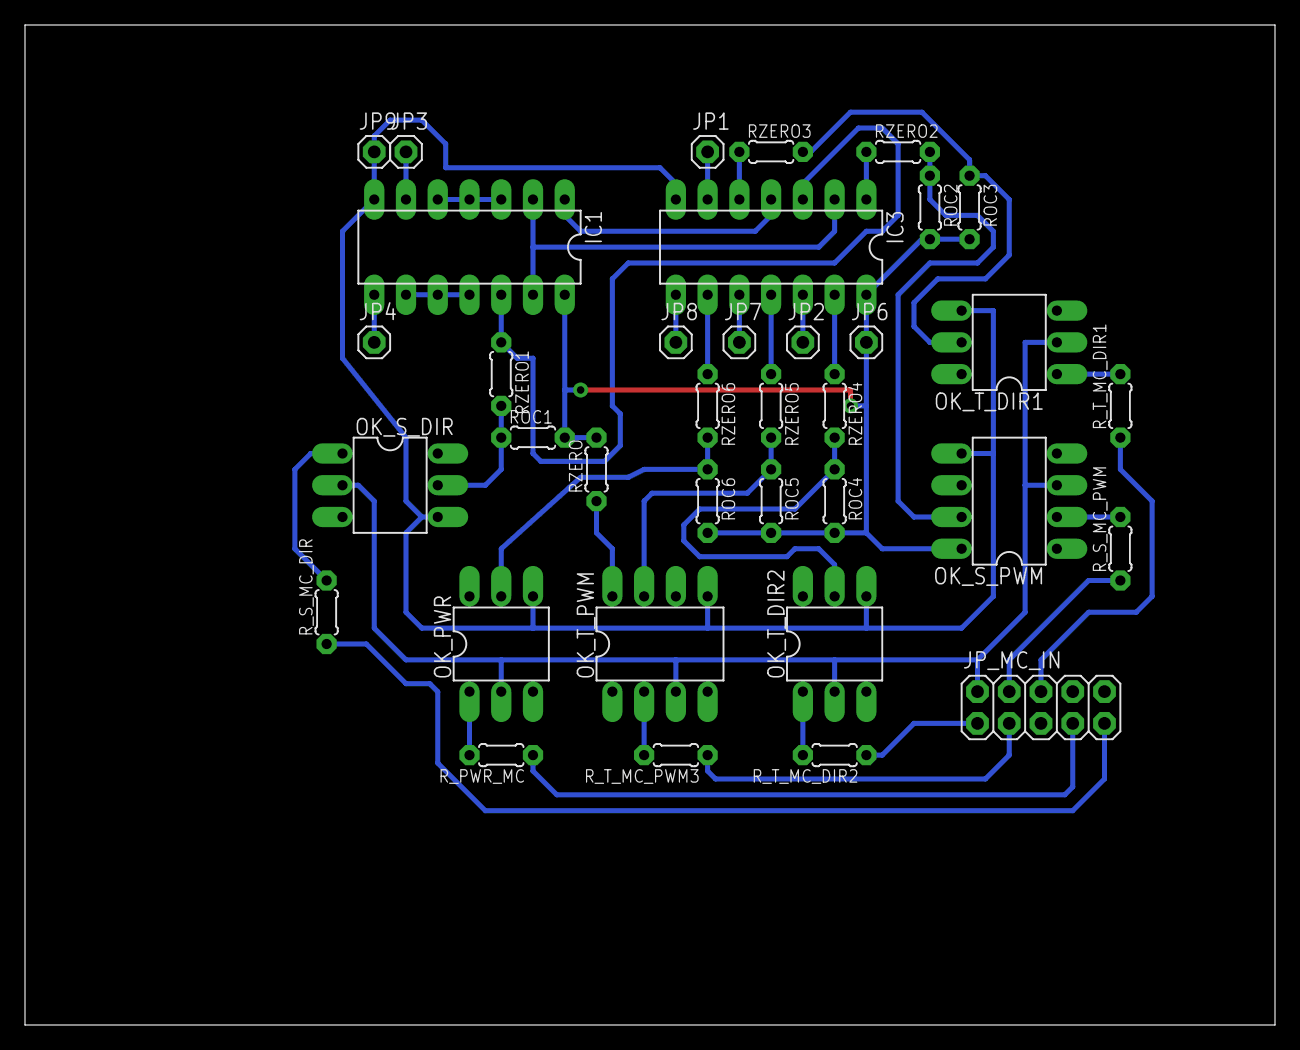
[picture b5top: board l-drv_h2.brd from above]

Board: 2 copper layers, 100.0 x 80.0 mm, 36 parts (0 on the bottom side), 38 nets.
